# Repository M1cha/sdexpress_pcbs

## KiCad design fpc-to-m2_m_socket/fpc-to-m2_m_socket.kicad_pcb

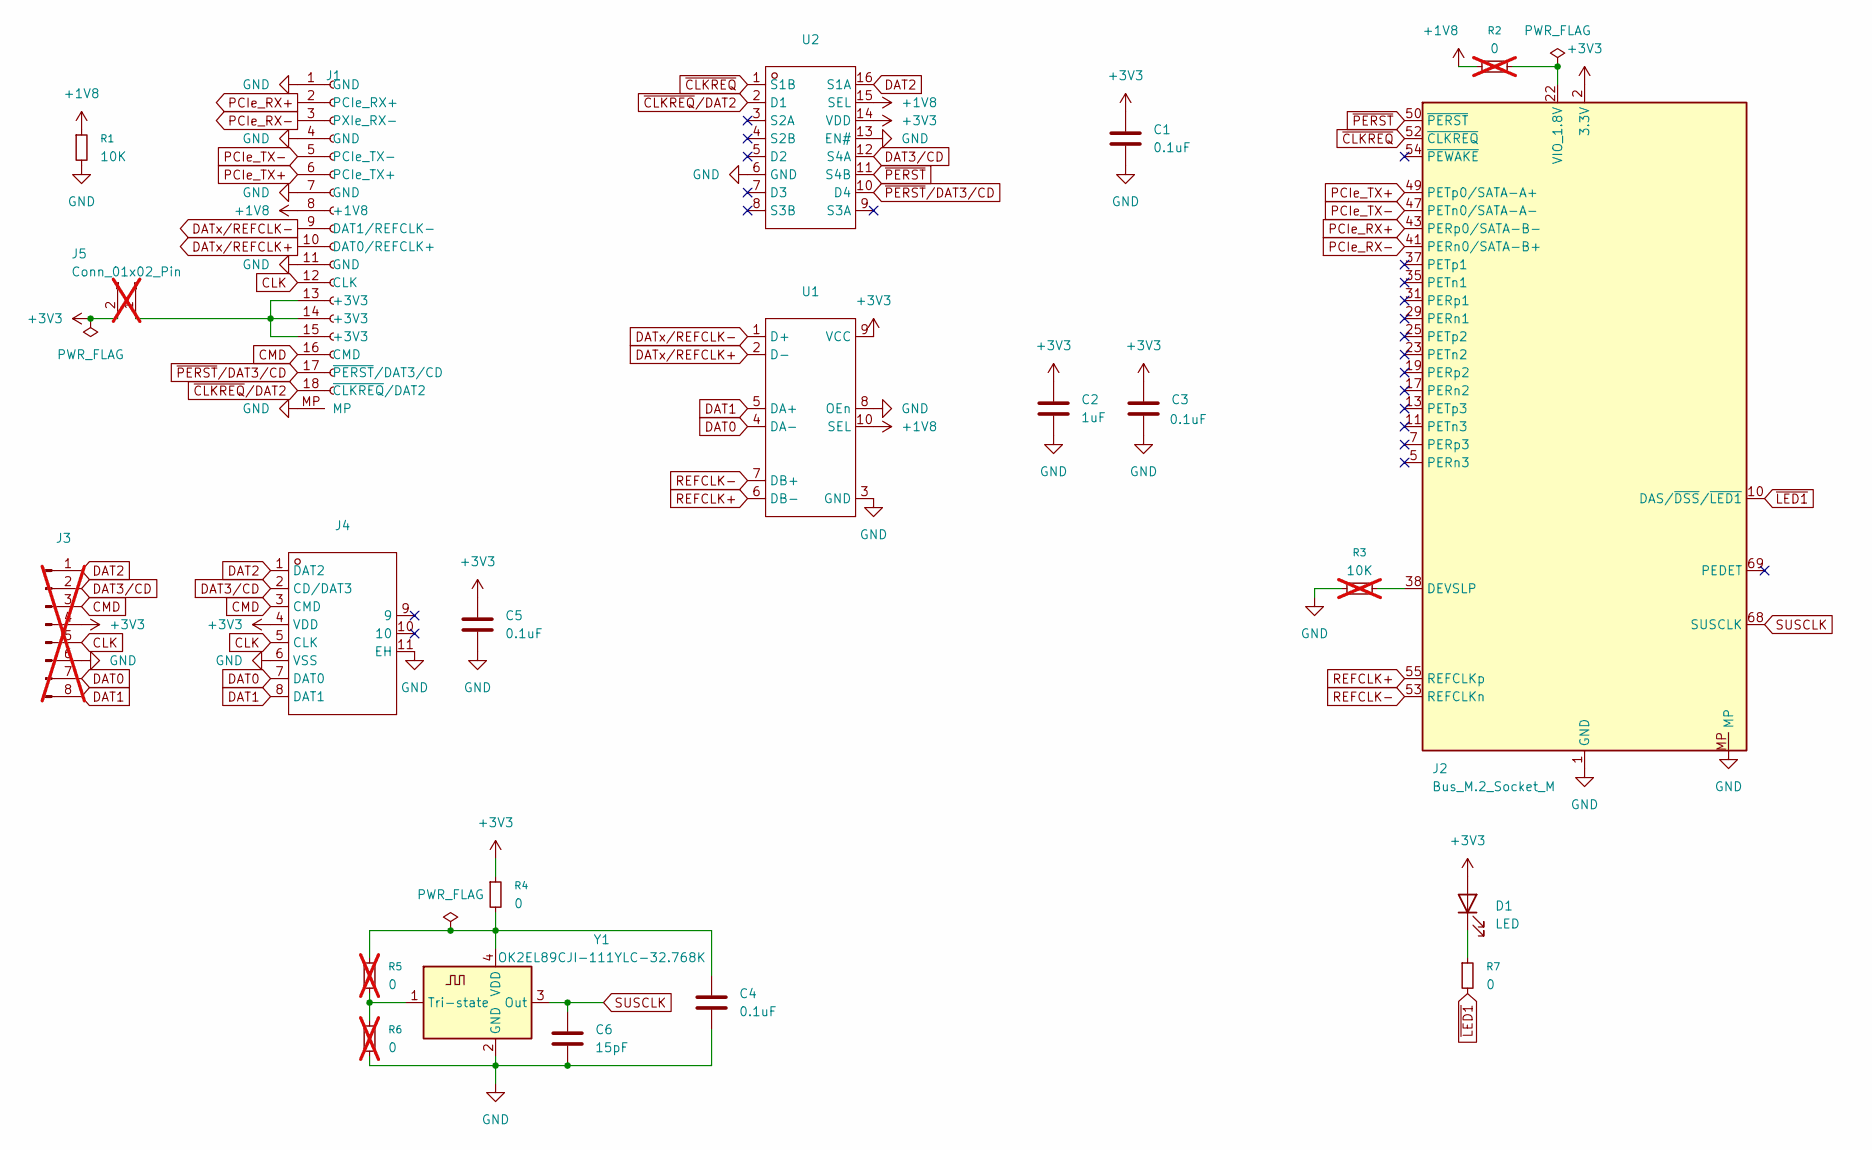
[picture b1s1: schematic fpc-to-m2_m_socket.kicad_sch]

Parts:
C1, C3, C4, C5: 0.1uF; C_0402_1005Metric
C2: 1uF; C_0402_1005Metric
C6: 15pF; C_0402_1005Metric
D1: LED; LED_0805_2012Metric
J1: FPC-SMD_18P-P1.00_JS_AFA07-S18XXX; JLC part C262743
J2: Bus_M.2_Socket_M; CONN-SMD_APCI0146-P001A
J3: PinHeader_1x08_P2.54mm_Vertical; not fitted
J4: TF-SMD_503398-1892; Manufacturer Part 5033981892; LCSC Part Name 自弹式 MicroSD卡(TF卡) 卡座
J5: Conn_01x02_Pin; PinHeader_1x02_P2.54mm_Vertical; not fitted
R1: 10K; R_0402_1005Metric
R2, R5, R6: 0; R_0402_1005Metric; not fitted
R3: 10K; R_0402_1005Metric; not fitted
R4, R7: 0; R_0402_1005Metric
U1: TMUXHS221NKGT; Manufacturer Part TMUXHS221NKGT; LCSC Part Name TMUXHS221 USB 2.0 480Mbps 2:1/1:2 多路复用器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
U2: tmux1574; Manufacturer Part TMUX1574RSVR; LCSC Part Name TMUX1574低电容、2:1(SPDT)4通道断电保护开关
Y1: OK2EL89CJI-111YLC-32.768K; OSC-SMD_4P-L3.2-W2.5-BL_TG-5006CE; JLC part C5280579

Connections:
+1V8: J1.8 (+1V8), R1.1, R2.1, U1.10 (SEL), U2.15 (SEL)
+3V3: C1.1, C2.1, C3.1, C5.1, D1.2 (A), J2.2 (3.3V), J2.4 (3.3V), J2.12 (3.3V), J2.14 (3.3V), J2.16 (3.3V), J2.18 (3.3V), J2.70 (3.3V), J2.72 (3.3V), J2.74 (3.3V), J3.4, J4.4 (VDD), J5.2, R4.1, U1.9 (VCC), U2.14 (VDD)
CLK: J1.12 (CLK), J3.5, J4.5 (CLK)
CMD: J1.16 (CMD), J3.3, J4.3 (CMD)
DAT0: J3.7, J4.7 (DAT0), U1.4 (DA-)
DAT1: J3.8, J4.8 (DAT1), U1.5 (DA+)
DAT2: J3.1, J4.1 (DAT2), U2.16 (S1A)
DAT3/CD: J3.2, J4.2 (CD/DAT3), U2.12 (S4A)
DATx/REFCLK+: J1.10 (DAT0/REFCLK+), U1.2 (D-)
DATx/REFCLK-: J1.9 (DAT1/REFCLK-), U1.1 (D+)
GND: C1.2, C2.2, C3.2, C4.2, C5.2, C6.2, J1.1 (GND), J1.4 (GND), J1.7 (GND), J1.11 (GND), J1.MP, J2.1 (GND), J2.3 (GND), J2.9 (GND), J2.15 (GND), J2.21 (GND), J2.27 (GND), J2.33 (GND), J2.39 (GND), J2.45 (GND), J2.51 (GND), J2.57 (GND), J2.71 (GND), J2.73 (GND), J2.75 (GND), J2.MP, J3.6, J4.6 (VSS), J4.11 (EH), R1.2, R3.1, R6.1, U1.3 (GND), U1.8 (OEn), U2.6 (GND), U2.13 (EN#), Y1.2 (GND)
unnamed: D1.1 (K), R7.1
unnamed: J2.38 (DEVSLP), R3.2
unnamed: J2.22 (VIO_1.8V), R2.2
unnamed: J1.13 (+3V3), J1.14 (+3V3), J1.15 (+3V3), J5.1
unnamed: R5.1, R6.2, Y1.1 (Tri-state)
unnamed: C4.1, R4.2, R5.2, Y1.4 (VDD)
PCIe_RX+: J1.2 (PCIe_RX+), J2.43 (PERp0/SATA-B-)
PCIe_RX-: J1.3 (PXIe_RX-), J2.41 (PERn0/SATA-B+)
PCIe_TX+: J1.6 (PCIe_TX+), J2.49 (PETp0/SATA-A+)
PCIe_TX-: J1.5 (PCIe_TX-), J2.47 (PETn0/SATA-A-)
REFCLK+: J2.55 (REFCLKp), U1.6 (DB-)
REFCLK-: J2.53 (REFCLKn), U1.7 (DB+)
SUSCLK: C6.1, J2.68 (SUSCLK), Y1.3 (Out)
~CLKREQ: J2.52 (~CLKREQ), U2.1 (S1B)
~CLKREQ/DAT2: J1.18 (~CLKREQ/DAT2), U2.2 (D1)
~LED1: J2.10 (DAS/~DSS/~LED1), R7.2
~PERST: J2.50 (~PERST), U2.11 (S4B)
~PERST/DAT3/CD: J1.17 (~PERST/DAT3/CD), U2.10 (D4)

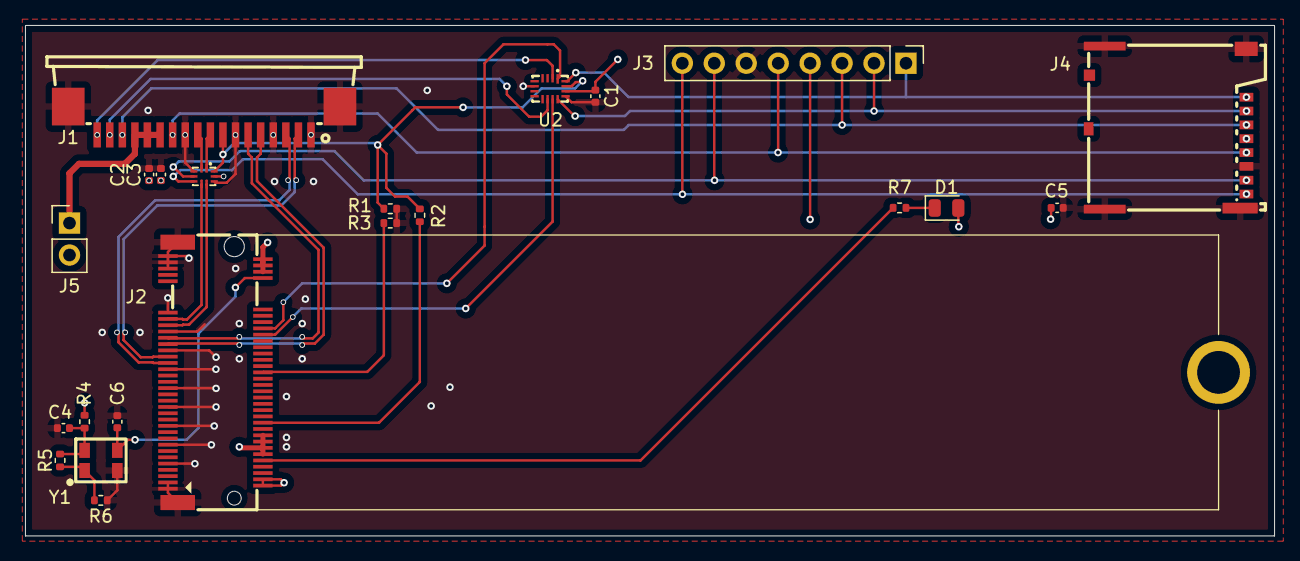
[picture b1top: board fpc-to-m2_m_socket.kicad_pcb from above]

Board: 6 copper layers, 99.3 x 40.6 mm, 22 parts (0 on the bottom side), 29 nets.

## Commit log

2025-05-03 WIP: initial adapter
2025-05-04 that should work
2025-05-04 reduce width
2025-05-10 finish usdex card
2025-05-11 almost done
2025-05-19 test
